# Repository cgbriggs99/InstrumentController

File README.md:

# InstrumentController
Controller for an instrument panel. Interfaces with MSFS.

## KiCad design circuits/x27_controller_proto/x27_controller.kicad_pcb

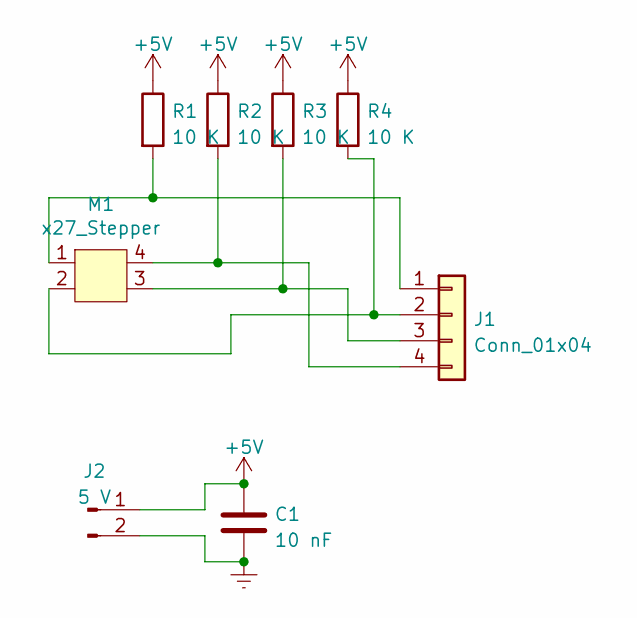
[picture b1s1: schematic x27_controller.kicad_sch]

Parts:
C1: 10 nF; C_0805_2012Metric_Pad1.18x1.45mm_HandSolder
J1: Conn_01x04; PinHeader_1x04_P2.54mm_Vertical
J2: 5 V; PinHeader_1x02_P2.54mm_Vertical
M1: x27_Stepper; Motor_x27-166
R1, R2, R3, R4: 10 K; R_0805_2012Metric_Pad1.20x1.40mm_HandSolder

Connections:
+5V: C1.1, J2.1, R1.1, R2.1, R3.1, R4.1
Earth: C1.2, J2.2
unnamed: J1.1, M1.1, R1.2
unnamed: J1.2, M1.2, R4.2
unnamed: J1.3, M1.3, R3.2
unnamed: J1.4, M1.4, R2.2

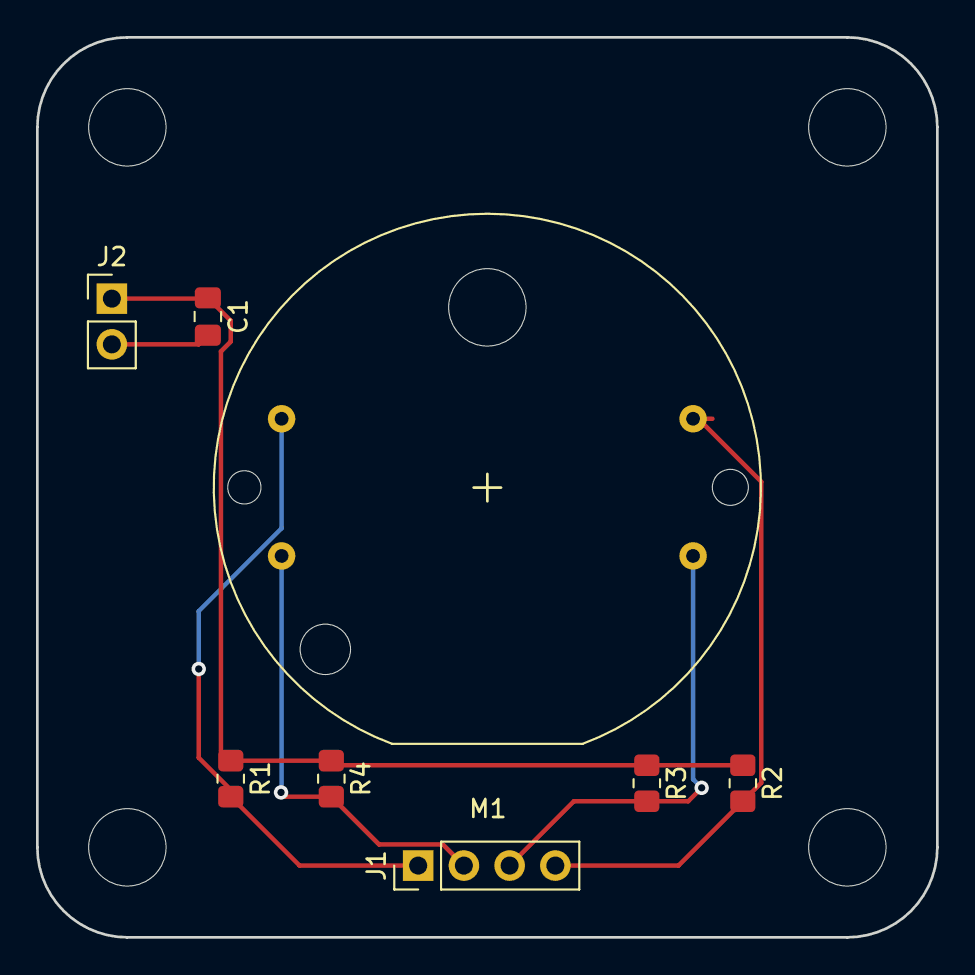
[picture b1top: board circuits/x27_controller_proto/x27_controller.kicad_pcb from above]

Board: 2 copper layers, 50.0 x 50.0 mm, 8 parts (0 on the bottom side), 6 nets.

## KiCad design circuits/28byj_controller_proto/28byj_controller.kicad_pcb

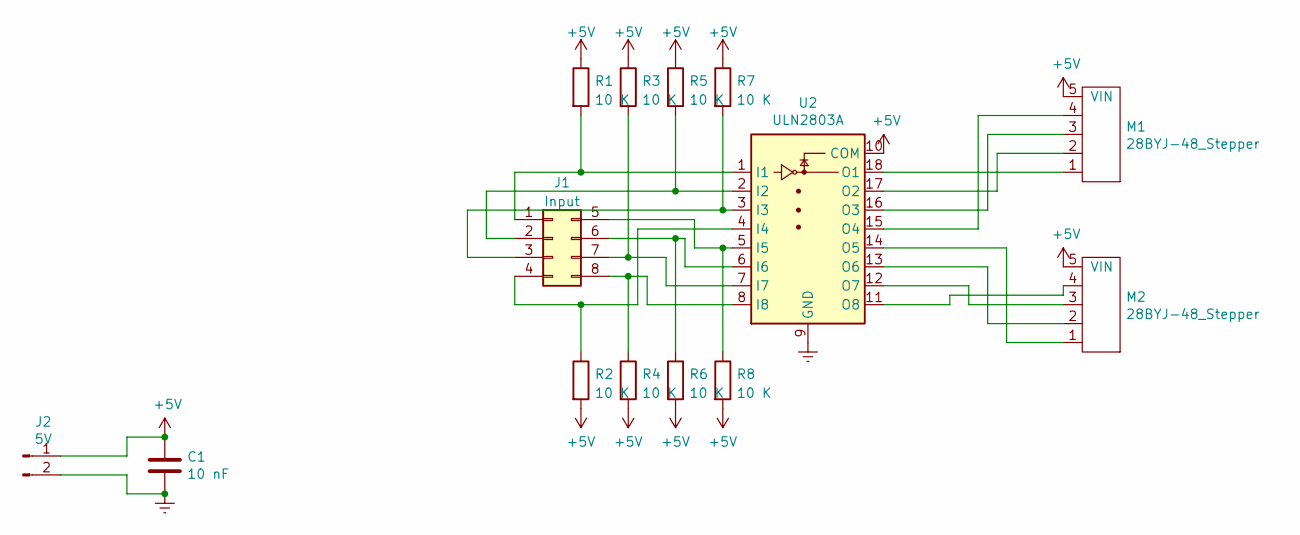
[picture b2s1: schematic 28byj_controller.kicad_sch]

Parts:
C1: 10 nF; C_0805_2012Metric_Pad1.18x1.45mm_HandSolder
J1: Input; PinHeader_2x04_P2.54mm_Vertical
J2: 5V; JST_XH_B2B-XH-AM_1x02_P2.50mm_Vertical
M1, M2: 28BYJ-48_Stepper; JST_XH_B5B-XH-A_1x05_P2.50mm_Vertical
R1, R2, R3, R4, R5, R6, R7, R8: 10 K; R_0805_2012Metric_Pad1.20x1.40mm_HandSolder
U2: ULN2803A; DIP-18_W7.62mm

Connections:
+5V: C1.1, J2.1, M1.5 (VIN), M2.5 (VIN), R1.1, R2.2, R3.1, R4.2, R5.1, R6.2, R7.1, R8.2, U2.10 (COM)
Earth: C1.2, J2.2, U2.9 (GND)
unnamed: J1.1, R1.2, U2.1 (I1)
unnamed: J1.2, R5.2, U2.2 (I2)
unnamed: J1.3, R7.2, U2.3 (I3)
unnamed: J1.4, R2.1, U2.4 (I4)
unnamed: J1.5, R8.1, U2.5 (I5)
unnamed: J1.6, R6.1, U2.6 (I6)
unnamed: J1.7, R3.2, U2.7 (I7)
unnamed: J1.8, R4.1, U2.8 (I8)
unnamed: M1.1, U2.18 (O1)
unnamed: M1.2, U2.17 (O2)
unnamed: M1.3, U2.16 (O3)
unnamed: M1.4, U2.15 (O4)
unnamed: M2.1, U2.14 (O5)
unnamed: M2.2, U2.13 (O6)
unnamed: M2.3, U2.12 (O7)
unnamed: M2.4, U2.11 (O8)

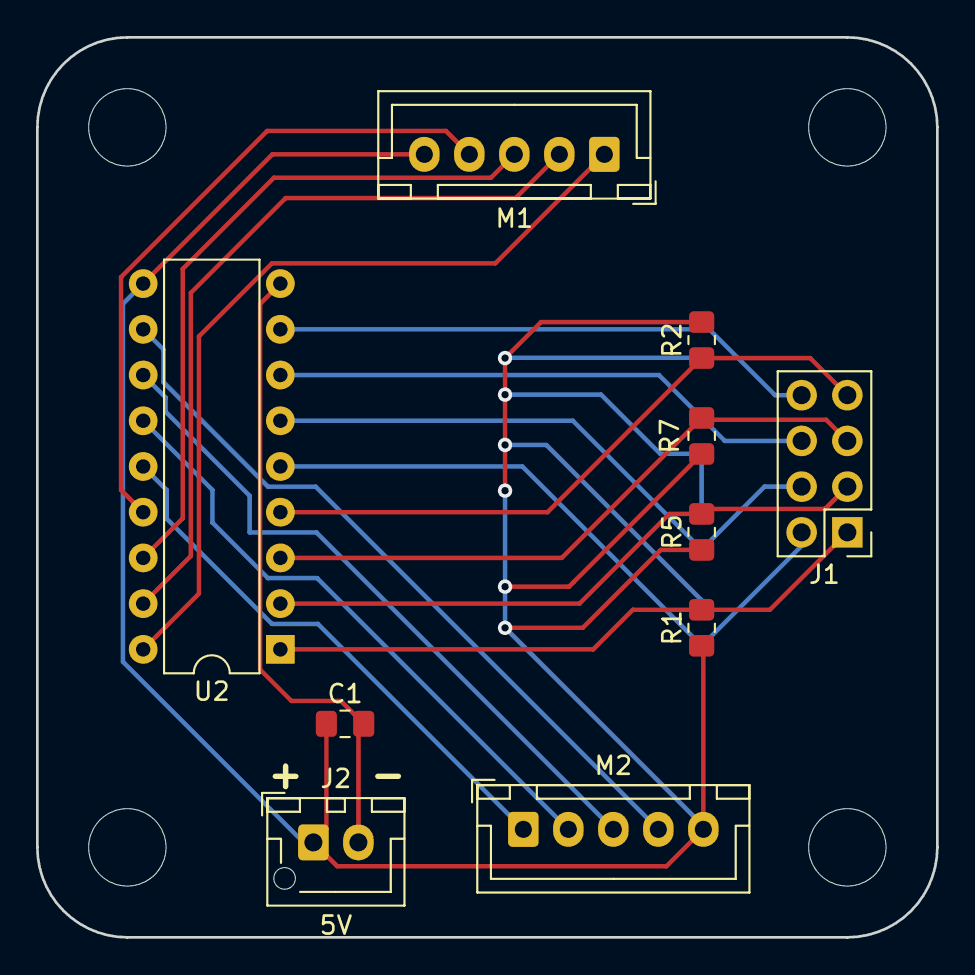
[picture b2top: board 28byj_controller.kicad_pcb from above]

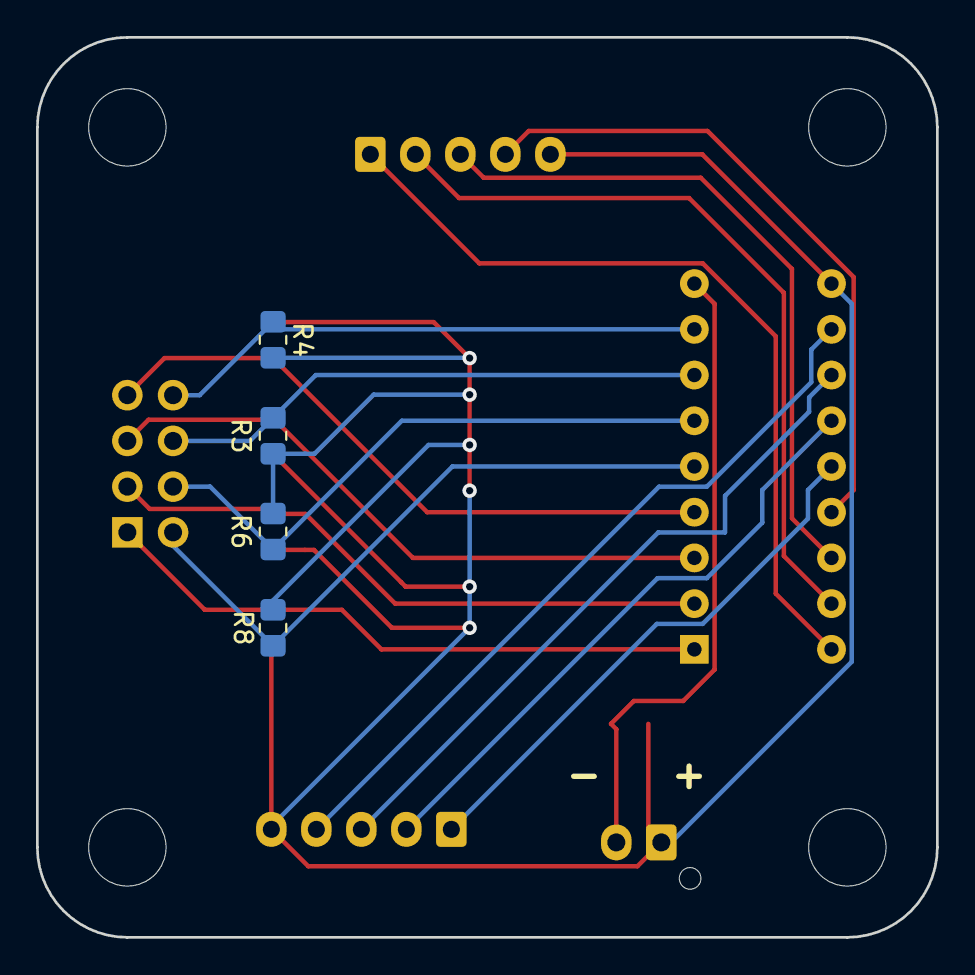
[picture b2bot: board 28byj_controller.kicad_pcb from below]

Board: 2 copper layers, 50.0 x 50.0 mm, 14 parts (4 on the bottom side), 18 nets.

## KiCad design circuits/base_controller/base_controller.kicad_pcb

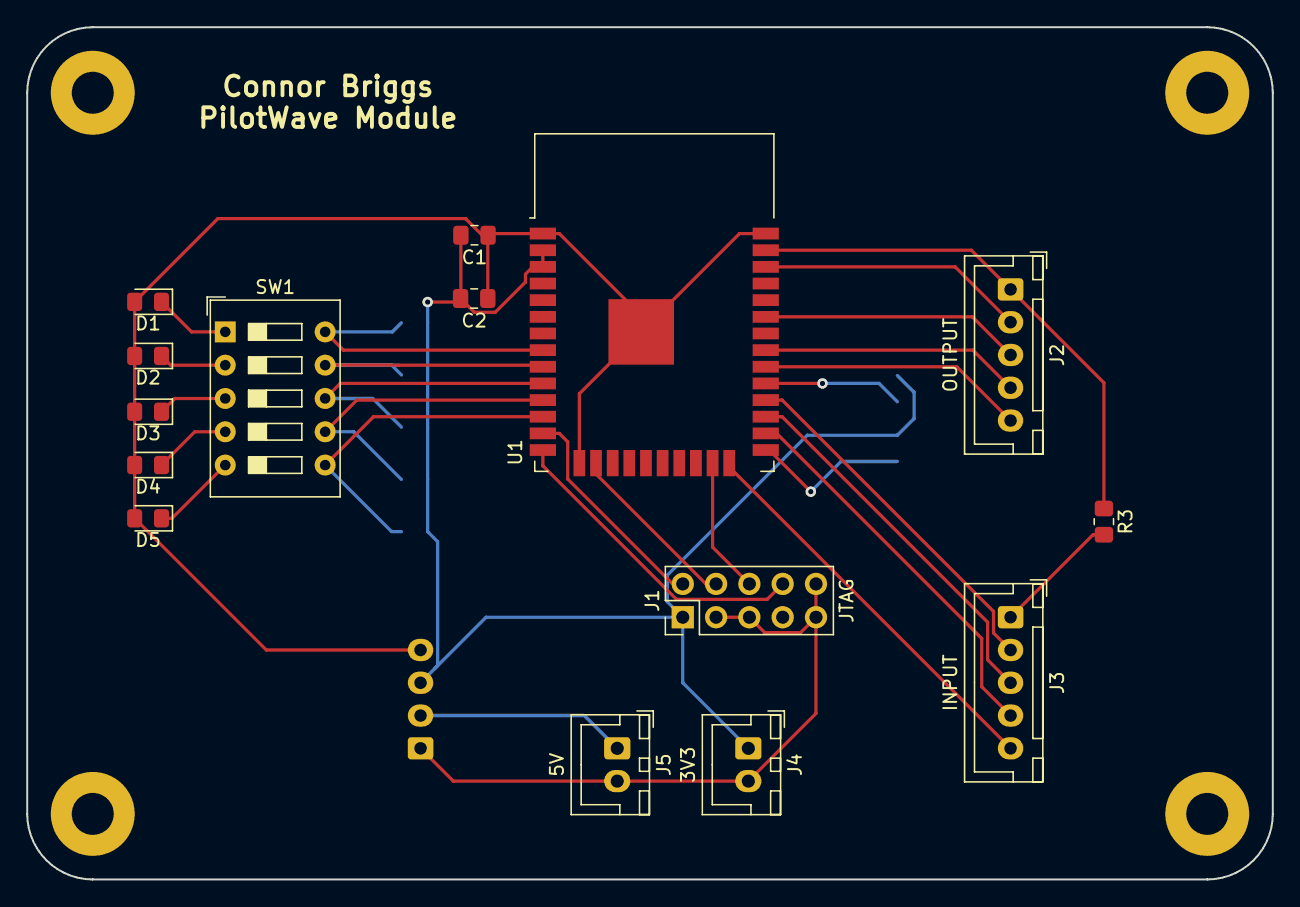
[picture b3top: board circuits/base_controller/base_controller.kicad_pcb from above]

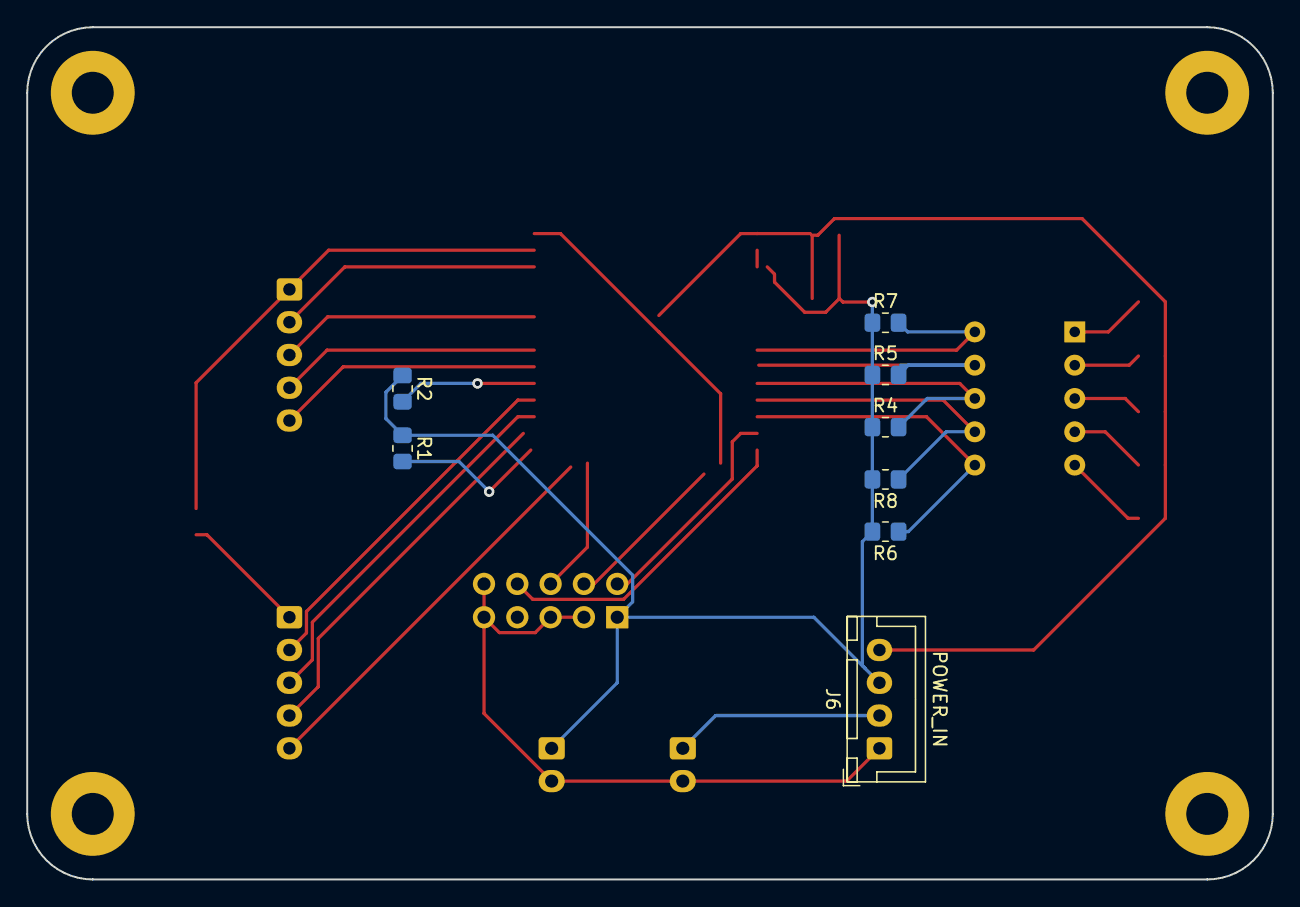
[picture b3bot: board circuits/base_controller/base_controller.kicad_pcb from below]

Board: 2 copper layers, 95.0 x 65.0 mm, 23 parts (8 on the bottom side), 29 nets.

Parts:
C1: 10 uF; C_0805_2012Metric_Pad1.18x1.45mm_HandSolder
C2: 0.1 uF; C_0805_2012Metric_Pad1.18x1.45mm_HandSolder
D1, D2, D3, D4, D5: DIODE; D_0805_2012Metric_Pad1.15x1.40mm_HandSolder
J1: JTAG; PinHeader_2x05_P2.54mm_Vertical
J2: OUTPUT; JST_XH_B5B-XH-A_1x05_P2.50mm_Vertical
J3: INPUT; JST_XH_B5B-XH-A_1x05_P2.50mm_Vertical
J4: 3V3; JST_XH_B2B-XH-A_1x02_P2.50mm_Vertical
J5: 5V; JST_XH_B2B-XH-A_1x02_P2.50mm_Vertical
J6: POWER_IN; JST_XH_B4B-XH-A_1x04_P2.50mm_Vertical
R1, R2: 10 K; R_0805_2012Metric_Pad1.20x1.40mm_HandSolder
R3: 1 K; R_0805_2012Metric_Pad1.20x1.40mm_HandSolder
R4, R5, R6, R7, R8: 4.7 k; R_0805_2012Metric_Pad1.20x1.40mm_HandSolder
SW1: DEV_CLASS; SW_DIP_SPSTx05_Slide_9.78x14.88mm_W7.62mm_P2.54mm
U1: ESP32-WROOM-32

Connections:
+5V: J5.1 (5V), J6.2
DATA_IO: J2.1, R3.1, U1.37 (IO23)
DEVCL_0: R7.2, SW1.10, U1.8 (IO32)
DEVCL_1: R5.2, SW1.9, U1.9 (IO33)
DEVCL_2: R4.2, SW1.8, U1.10 (IO25)
DEVCL_3: R8.1, SW1.7, U1.11 (IO26)
DEVCL_4: R6.1, SW1.6, U1.12 (IO27)
EN: C1.2, C2.2, J1.1 (VTref), J4.1 (3V3), J6.3, R1.1, R2.1, R4.1, R5.1, R6.2, R7.1, R8.2, U1.2 (VDD), U1.3 (EN)
Earth: C1.1, C2.1, D1.2 (A), D2.2 (A), D3.2 (A), D4.2 (A), D5.2 (A), J1.3 (GND), J1.5 (GND), J1.9 (GNDDetect), J1.10 (~RESET), J4.2 (GND), J5.2 (GND), J6.1, J6.4, U1.1 (GND), U1.15 (GND), U1.38 (GND), U1.39 (GND)
IO0: R1.2, U1.25 (IO0)
IO5: R2.2, U1.29 (IO5)
MR_1: J2.5, U1.30 (IO18)
MR_2: J3.5, U1.24 (IO2)
MTCK: J1.4 (SWDCLK/TCK), U1.16 (IO13)
MTDI: J1.8 (NC/TDI), U1.14 (IO12)
MTDO: J1.6 (SWO/TDO), U1.23 (IO15)
MTMS: J1.2 (SWDIO/TMS), U1.13 (IO14)
unnamed: D1.1 (K), SW1.1
unnamed: D2.1 (K), SW1.2
unnamed: D3.1 (K), SW1.3
unnamed: D4.1 (K), SW1.4
unnamed: D5.1 (K), SW1.5
unnamed: J3.1, R3.2
OE_1: J2.4, U1.31 (IO19)
PL_2: J3.4, U1.26 (IO4)
SHCP_1: J2.2, U1.36 (IO22)
SHCP_2: J3.2, U1.28 (IO17)
STCP_1: J2.3, U1.33 (IO21)
STCP_2: J3.3, U1.27 (IO16)

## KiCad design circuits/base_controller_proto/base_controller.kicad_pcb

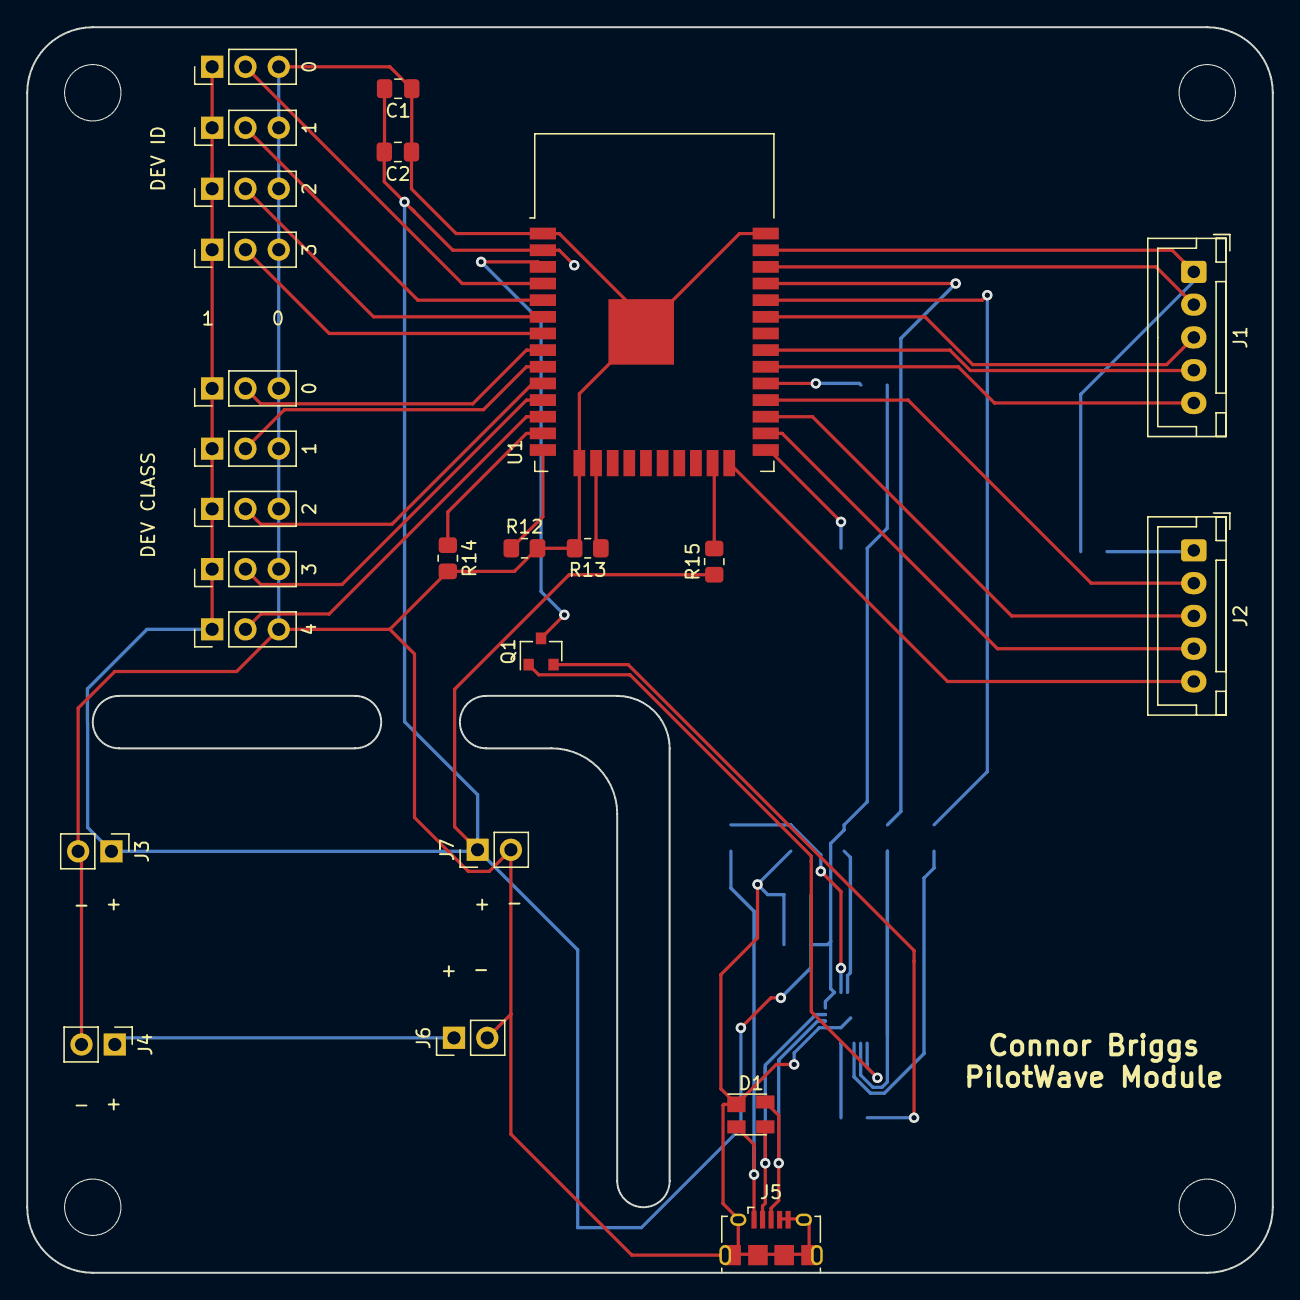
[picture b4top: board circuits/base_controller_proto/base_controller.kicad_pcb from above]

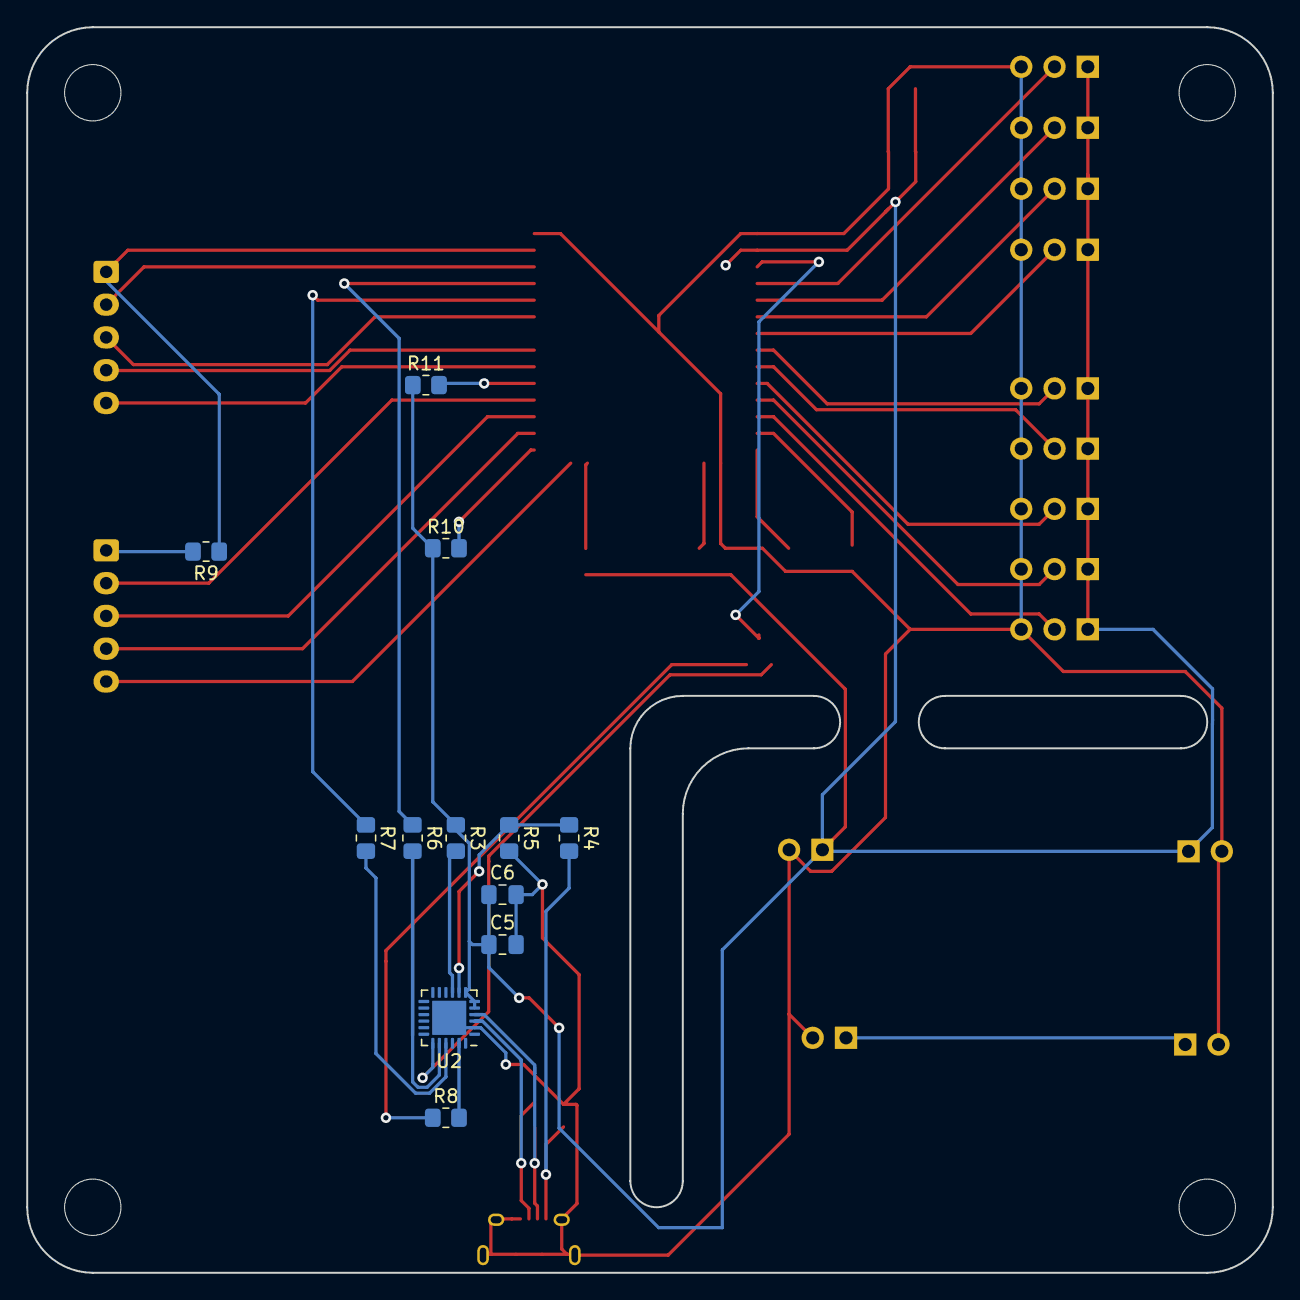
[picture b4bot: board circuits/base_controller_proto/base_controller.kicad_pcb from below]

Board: 2 copper layers, 95.0 x 95.0 mm, 37 parts (12 on the bottom side), 41 nets.

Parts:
C1: 10 uF; C_0805_2012Metric_Pad1.18x1.45mm_HandSolder
C2, C6: 0.1 uF; C_0805_2012Metric_Pad1.18x1.45mm_HandSolder
C5: 4.7 uF; C_0805_2012Metric_Pad1.18x1.45mm_HandSolder
D1: SP0503BAHT; SOT-143
J1: OUTPUT; JST_XH_B5B-XH-A_1x05_P2.50mm_Vertical
J2: INPUT; JST_XH_B5B-XH-A_1x05_P2.50mm_Vertical
J3: 3V3 OUT; PinHeader_1x02_P2.54mm_Vertical
J4: 5V OUT; PinHeader_1x02_P2.54mm_Vertical
J5: USB_B_Micro; USB_Micro-B_Amphenol_10118194_Horizontal
J6: 5V IN; PinHeader_1x02_P2.54mm_Vertical
J7: 3V3 IN; PinHeader_1x02_P2.54mm_Vertical
JP1, JP6: 0; PinHeader_1x03_P2.54mm_Vertical
JP2, JP7: 1; PinHeader_1x03_P2.54mm_Vertical
JP3, JP8: 2; PinHeader_1x03_P2.54mm_Vertical
JP4, JP9: 3; PinHeader_1x03_P2.54mm_Vertical
JP5: 4; PinHeader_1x03_P2.54mm_Vertical
Q1: S8050; SOT-23
R3, R6, R7, R9: 1 K; R_0805_2012Metric_Pad1.20x1.40mm_HandSolder
R4: 22.1 K; R_0805_2012Metric_Pad1.20x1.40mm_HandSolder
R5: 47.5 K; R_0805_2012Metric_Pad1.20x1.40mm_HandSolder
R8, R10, R11, R12, R13, R14, R15: 10 K; R_0805_2012Metric_Pad1.20x1.40mm_HandSolder
U1: ESP32-WROOM-32
U2: CP2102N-A01-GQFN24; QFN-24-1EP_4x4mm_P0.5mm_EP2.6x2.6mm

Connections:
+3V3: C1.2, C2.2, C5.1, C6.1, J3.1, J7.1, JP1.1 (A), JP2.1 (A), JP3.1 (A), JP4.1 (A), JP5.1 (A), JP6.1 (A), JP7.1 (A), JP8.1 (A), JP9.1 (A), R3.1, R10.1, R11.1, R15.1, U1.2 (VDD), U2.5 (VIO), U2.6 (VDD), U2.7 (REGIN)
+5V: J4.1, J6.1
DATA_IO: J1.1, R9.1, U1.37 (IO23)
DEVCL_0: JP1.2 (C), U1.8 (IO32)
DEVCL_1: JP2.2 (C), U1.9 (IO33)
DEVCL_2: JP3.2 (C), U1.10 (IO25)
DEVCL_3: JP4.2 (C), U1.11 (IO26)
DEVCL_4: JP5.2 (C), U1.12 (IO27)
DEVID_0: JP6.2 (C), U1.4 (SENSOR_VP)
DEVID_1: JP7.2 (C), U1.5 (SENSOR_VN)
DEVID_2: JP8.2 (C), U1.6 (IO34)
DEVID_3: JP9.2 (C), U1.7 (IO35)
EN: Q1.3 (C), U1.3 (EN)
Earth: C1.1, C2.1, C5.2, C6.2, D1.1 (A), J3.2, J4.2, J5.4 (ID), J5.5 (GND), J5.6 (Shield), J6.2, J7.2, JP1.3 (B), JP2.3 (B), JP3.3 (B), JP4.3 (B), JP5.3 (B), JP6.3 (B), JP7.3 (B), JP8.3 (B), JP9.3 (B), R5.2, R12.2, R13.2, R14.2, U1.1 (GND), U1.15 (GND), U1.38 (GND), U1.39 (GND), U2.2 (GND), U2.25 (GND)
IO0: R10.2, U1.25 (IO0)
IO5: R11.2, U1.29 (IO5)
MR_1: J1.5, U1.30 (IO18)
MR_2: J2.5, U1.24 (IO2)
MTCK: R13.1, U1.16 (IO13)
MTDI: R12.1, U1.14 (IO12)
MTDO: R15.2, U1.23 (IO15)
MTMS: R14.1, U1.13 (IO14)
unnamed: D1.2 (K), J5.1 (VBUS), R4.2
unnamed: D1.3 (K), J5.2 (D-), U2.4 (D-)
unnamed: D1.4 (K), J5.3 (D+), U2.3 (D+)
unnamed: J2.1, R9.2
unnamed: Q1.1 (E), U2.19 (RTS)
unnamed: Q1.2 (B), R8.1
unnamed: R3.2, U2.9 (~RSTb)
unnamed: R4.1, R5.1, U2.8 (VBUS)
unnamed: R6.2, U2.20 (RXD)
unnamed: R7.2, U2.21 (TXD)
unnamed: R8.2, U2.23 (DTR)
OE_1: J1.4, U1.31 (IO19)
PL_2: J2.4, U1.26 (IO4)
RXD0: R7.1, U1.34 (RXD0/IO3)
SHCP_1: J1.2, U1.36 (IO22)
SHCP_2: J2.2, U1.28 (IO17)
STCP_1: J1.3, U1.33 (IO21)
STCP_2: J2.3, U1.27 (IO16)
TXD0: R6.1, U1.35 (TXD0/IO1)

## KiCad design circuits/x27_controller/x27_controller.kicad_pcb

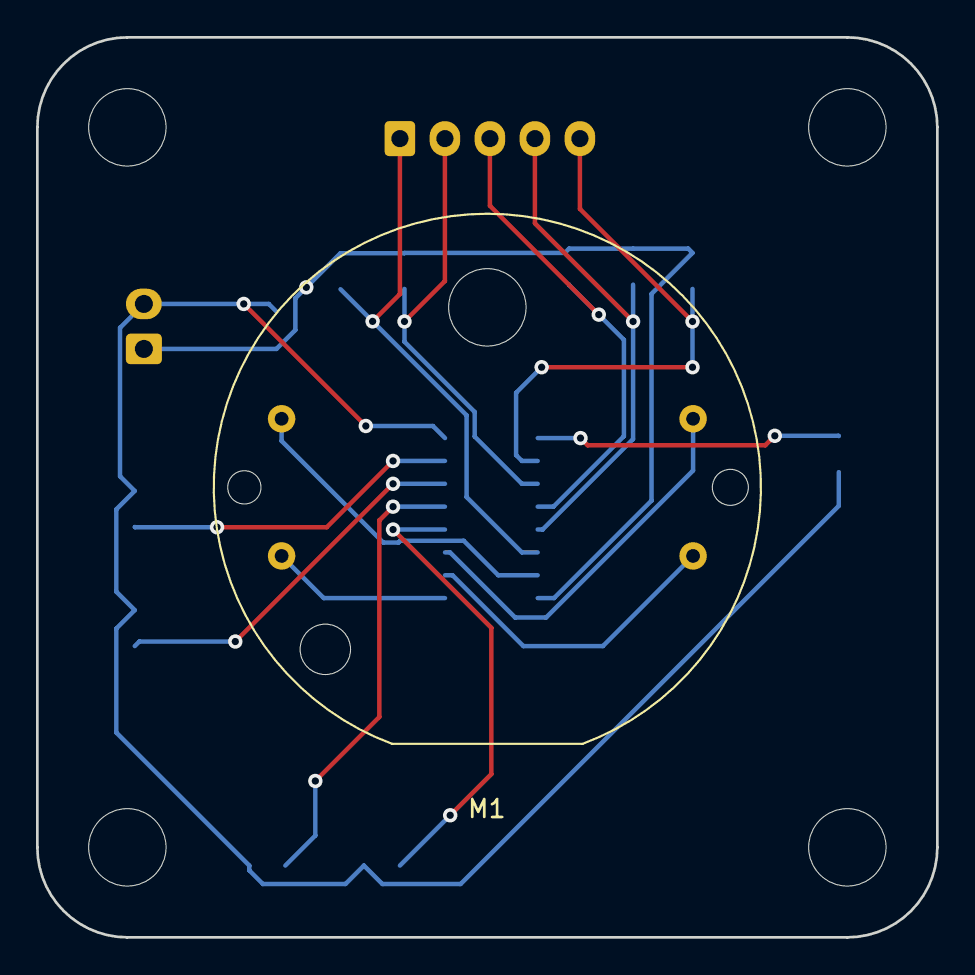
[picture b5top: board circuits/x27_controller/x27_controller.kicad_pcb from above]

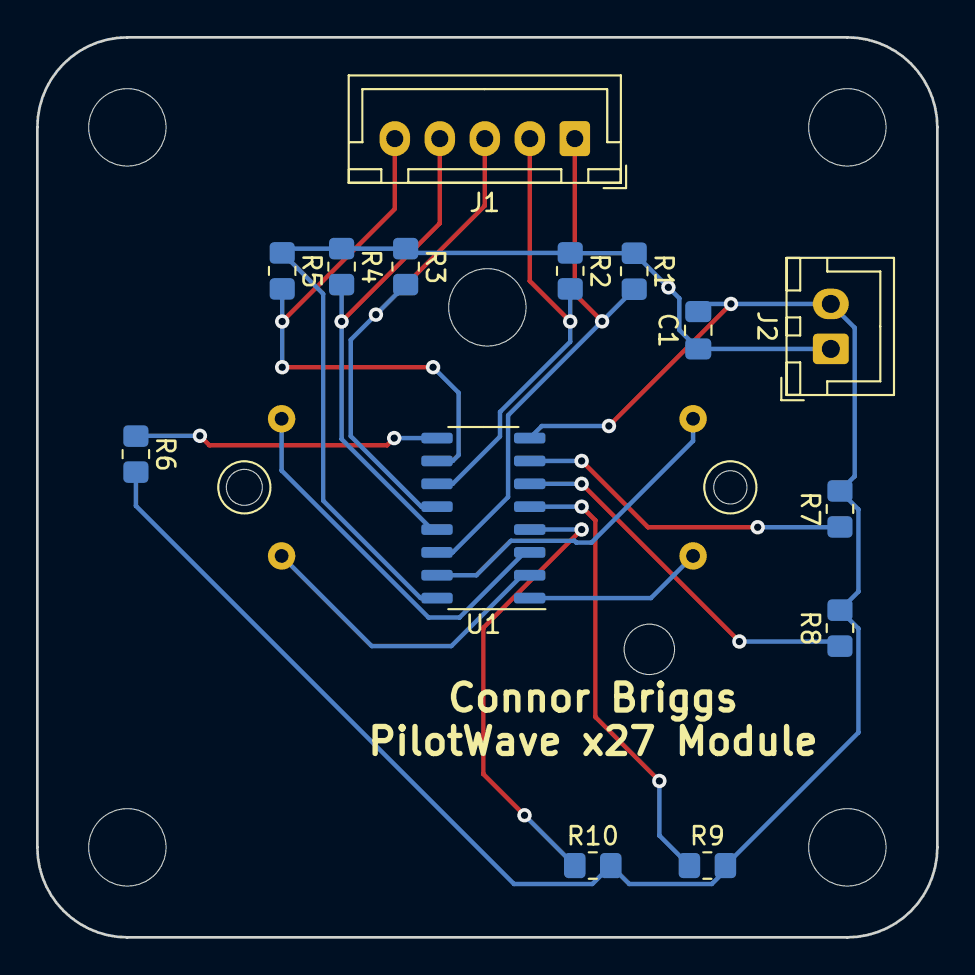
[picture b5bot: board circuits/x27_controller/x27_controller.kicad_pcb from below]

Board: 2 copper layers, 50.0 x 50.0 mm, 15 parts (14 on the bottom side), 16 nets.

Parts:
C1: 10 nF; C_0805_2012Metric_Pad1.18x1.45mm_HandSolder
J1: INPUT; JST_XH_B5B-XH-A_1x05_P2.50mm_Vertical
J2: 5V; JST_XH_B2B-XH-A_1x02_P2.50mm_Vertical
M1: x27_Stepper; Motor_x27-166
R1, R2, R3, R4, R5: 10K; R_0805_2012Metric_Pad1.20x1.40mm_HandSolder
R6, R7, R8, R9, R10: 1K; R_0805_2012Metric_Pad1.20x1.40mm_HandSolder
U1: 74HC595; SO-16_3.9x9.9mm_P1.27mm

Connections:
+5V: C1.1, J2.1, R1.1, R2.1, R3.1, R4.1, R5.1, U1.16
Earth: C1.2, J2.2, R6.2, R7.2, R8.2, R9.2, R10.2, U1.8
unnamed: J1.1, R1.2, U1.14
unnamed: J1.2, R2.2, U1.11
unnamed: J1.3, R3.2, U1.12
unnamed: J1.4, R4.2, U1.13
unnamed: J1.5, R5.2, U1.10
unnamed: M1.1, U1.15
unnamed: M1.2, U1.1
unnamed: M1.3, U1.2
unnamed: M1.4, U1.3
unnamed: R6.1, U1.9
unnamed: R7.1, U1.7
unnamed: R8.1, U1.6
unnamed: R9.1, U1.5
unnamed: R10.1, U1.4

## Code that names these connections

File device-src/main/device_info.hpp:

#ifndef __DEVICE_INFO_HPP__
#define __DEVICE_INFO_HPP__

#include <stdint.h>

// Pins for the device class.
#define DEVCL_0 25
#define DEVCL_1 26
#define DEVCL_2 27
#define DEVCL_3 32
#define DEVCL_4 33

// Pins for the headers
#define DATA_IO 23
#define SHCP_1 22
#define SHCP_2 17
#define STCP_1 21
#define STCP_2 16
#define OE_1 19
#define PL_2 4
#define __MR_1 18
#define __MR_2 2

#define MOTOR1 23
#define MOTOR2 22
#define MOTOR3 21
#define MOTOR4 19
#define MOTOR5 18
#define MOTOR6 17
#define MOTOR7 16
#define MOTOR8 4


typedef enum {
  // Test drivers.
  TEST_X27 = 0,
  TEST_28BYJ = 1,
  TEST_7S_DISPLAY = 2,
  
  // Device drivers.
  // Output devices.
  ALTIMETER = 3,
  SPEDOMETER = 4,
  TACHOMETER = 5,
  CLOCK = 6,
  FUEL_GAUGE = 7,
  OIL_GAUGE = 8,

  // Input devices
  RADIO = 9,
  ENGINE_STARTER = 10,
} device_class_t;

/**
 * @struct device_info_t
 * Holds the device info.
 */
typedef struct {
  /**
   * @var devclass
   * 
   * Holds the device class.
   */
  device_class_t devclass;

  /**
   * @var devid
   * 
   * Holds the device id. This is simply the MAC address of the adapter.
   */
  uint64_t devid;
} device_info_t;

/**
 * Get the device info. 
 */
extern device_info_t get_device_info(void);
    


#endif

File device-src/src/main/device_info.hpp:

#ifndef __DEVICE_INFO_HPP__
#define __DEVICE_INFO_HPP__

#include <stdint.h>

// Pins for the device id and the device class.
// These four are input-only.
#define DEVID_0 34
#define DEVID_1 35
#define DEVID_2 36
#define DEVID_3 39

#define DEVCL_0 25
#define DEVCL_1 26
#define DEVCL_2 27
#define DEVCL_3 32
#define DEVCL_4 33


// Header pins. Note that header 3 may have some issues at the moment due to strapping.
#define HEADER1_0 23
#define HEADER1_1 22
#define HEADER1_2 3
#define HEADER1_3 1

#define HEADER2_0 21
#define HEADER2_1 19
#define HEADER2_2 18
#define HEADER2_3 17

#define HEADER3_0 2
#define HEADER3_1 4
#define HEADER3_2 5
#define HEADER3_3 16

typedef enum {
  // Test drivers.
  TEST_X27 = 0,
  TEST_28BYJ = 1,
  TEST_7S_DISPLAY = 2,
  
  // Device drivers.
  ALTIMETER = 3,
  SPEDOMETER = 4,
  TACHOMETER = 5,
  CLOCK = 6,
  FUEL_GAUGE = 7,
  OIL_GAUGE = 8,
  RADIO = 9,
} device_class_t;

// Hold the device info.
typedef struct {
  device_class_t devclass;
  uint8_t devid;
  const char *topic;
  
} device_info_t;


extern device_info_t get_device_info(void);
    


#endif

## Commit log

2023-08-04 Added some files.
2023-08-04 Added circuits for the central controller.
2023-08-04 Small edit
2023-08-05 Made break-out boards for the motors
2023-08-16 Restructured files.
2023-08-16 Added some drivers
2023-08-16 Code compiles
2023-12-29 Big changes
2023-12-30 Shift now works
2023-12-31 Code works
2024-01-01 Device uses mac address as id
2024-06-12 Big updates
2024-06-12 Fixed type conversions
2024-06-15 Add some comments.
2024-06-15 Fixed a few bugs
2024-06-16 Added debuggin
2024-06-26 Added debug parser.
2024-06-26 Commented the code.
2024-06-26 Finished commenting.
2024-06-28 Fixed a bug.
2024-06-28 Moved wifi info to a separate file
2024-06-28 Hide wifi secrets.
2024-06-28 Added comments.
2024-06-28 Fixed gitignore.
2024-06-28 Fixing .gitignore
2024-06-28 Fixing gitignore
2024-06-29 Removed shift register from 28byj
2024-07-02 Ignore more files.
2024-07-02 Code works and is tested on waveforms.
2024-07-03 output open drain
2024-07-07 Modified some circuits.
2024-07-07 Added more pullups
